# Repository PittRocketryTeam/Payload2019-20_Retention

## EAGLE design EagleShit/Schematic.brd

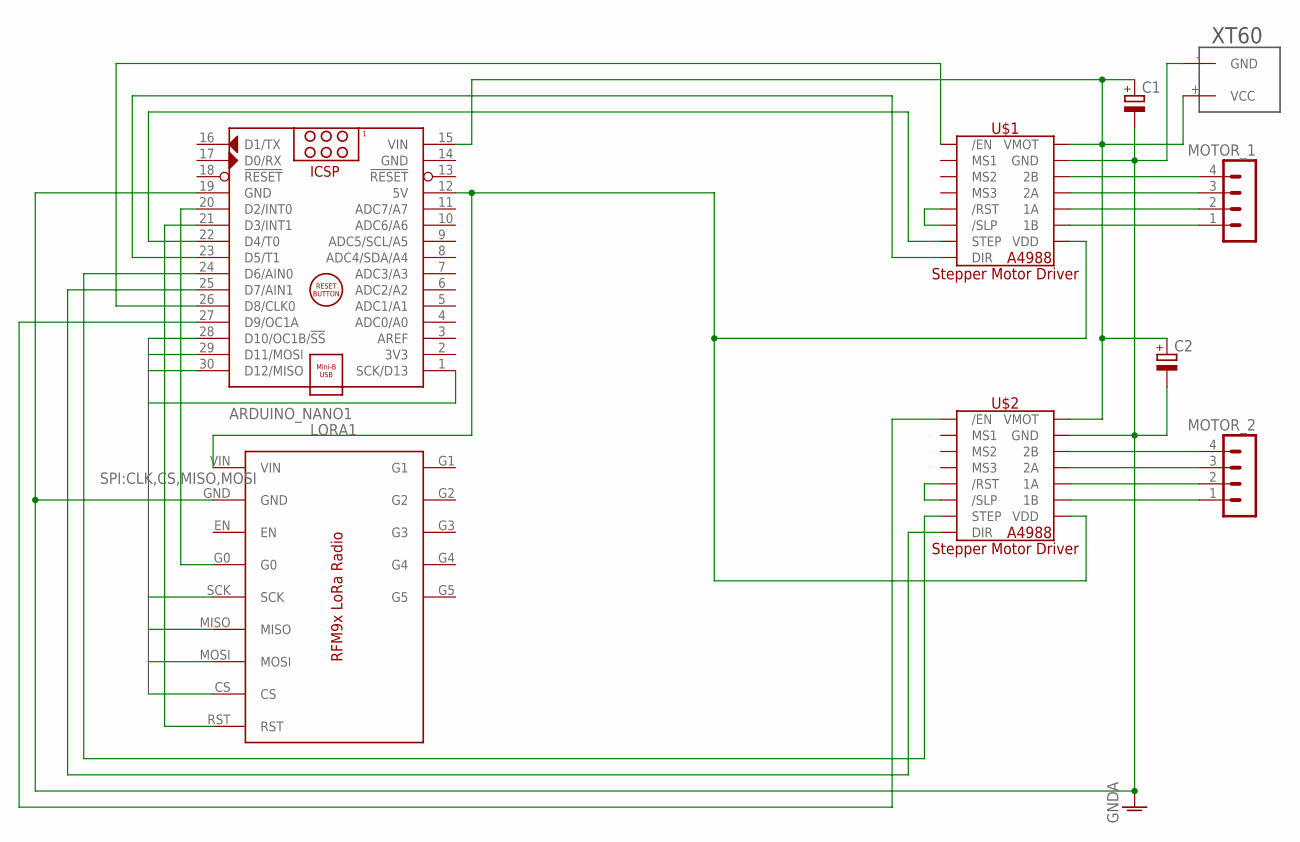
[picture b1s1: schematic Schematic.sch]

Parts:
ARDUINO_NANO1: ARDUINO_NANO
C1, C2: CPOL-EUE2,5-6E; E2,5-6E
LORA1: RFM9X_LORA
MOTOR_1, MOTOR_2: MA04-1
U$1, U$2: A4988_STEP
U$3: XT60_XT60

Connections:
CLK: ARDUINO_NANO1.1 (SCK/D13), LORA1.SCK
CS: ARDUINO_NANO1.28 (D10/OC1B/!SS), LORA1.CS
GND: ARDUINO_NANO1.14 (GND)
GNDA: ARDUINO_NANO1.19 (GND), C1.-, C2.-, LORA1.GND, U$1.GND, U$1.GND2 (GND), U$2.GND, U$2.GND2 (GND), U$3.- (GND)
MISO: ARDUINO_NANO1.30 (D12/MISO), LORA1.MISO
MOSI: ARDUINO_NANO1.29 (D11/MOSI), LORA1.MOSI
unnamed: ARDUINO_NANO1.21 (D3/INT1), LORA1.RST
unnamed: ARDUINO_NANO1.20 (D2/INT0), LORA1.G0
unnamed: ARDUINO_NANO1.12 (5V), LORA1.VIN, U$1.VDD, U$2.VDD
unnamed: ARDUINO_NANO1.26 (D8/CLK0), U$1./EN
unnamed: U$1./RST, U$1./SLP
unnamed: U$2./RST, U$2./SLP
unnamed: ARDUINO_NANO1.22 (D4/T0), U$1.STEP
unnamed: ARDUINO_NANO1.23 (D5/T1), U$1.DIR
unnamed: ARDUINO_NANO1.24 (D6/AIN0), U$2.STEP
unnamed: ARDUINO_NANO1.25 (D7/AIN1), U$2.DIR
unnamed: ARDUINO_NANO1.15 (VIN), C1.+, C2.+, U$1.VMOT, U$2.VMOT, U$3.+ (VCC)
unnamed: ARDUINO_NANO1.27 (D9/OC1A), U$2./EN
unnamed: MOTOR_1.4, U$1.2B
unnamed: MOTOR_1.3, U$1.2A
unnamed: MOTOR_1.2, U$1.1A
unnamed: MOTOR_1.1, U$1.1B
unnamed: MOTOR_2.4, U$2.2B
unnamed: MOTOR_2.3, U$2.2A
unnamed: MOTOR_2.2, U$2.1A
unnamed: MOTOR_2.1, U$2.1B

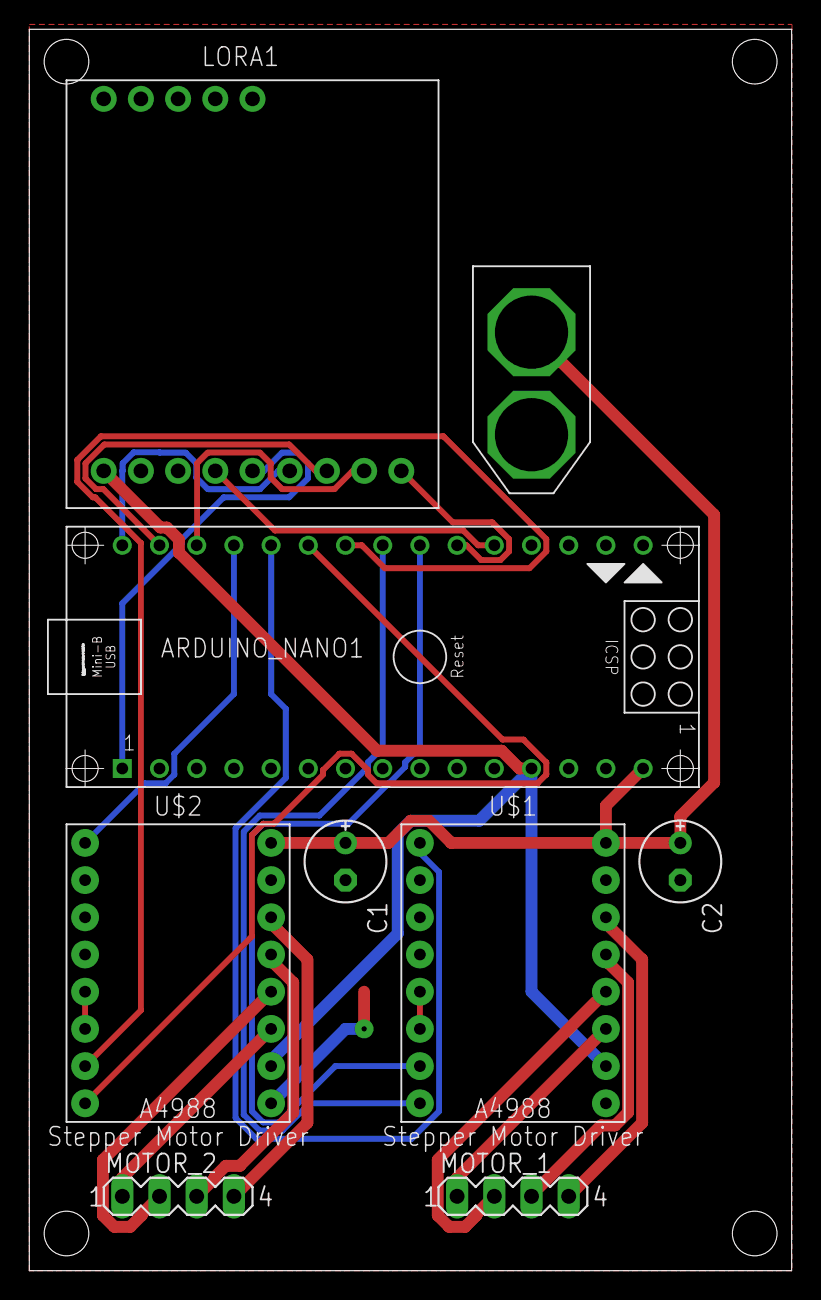
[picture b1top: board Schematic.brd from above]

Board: 2 copper layers, 52.1 x 84.8 mm, 9 parts (0 on the bottom side), 25 nets.

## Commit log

2020-01-19 just an initial test from last years code.
2020-01-20 All the eagle things - rocket side
2020-01-20 some important associated libraries!
    Allows you to add arduino nano, lora, and a4988 drivers to schematic w/ proper board pin locations and dimensions
2020-01-24 Lipo Connector Eagle Library
2020-01-24 New schematic with board!
2020-01-24 unnessary
2020-02-06 This code works; only minor changes remain
2020-02-07 Multi-button functionality
2020-02-07 Files for ordering PCB
2020-02-10 Updated to continuous execution
2020-02-10 Added Enable Pin Map/Code
2020-02-11 Added Enable Pins
